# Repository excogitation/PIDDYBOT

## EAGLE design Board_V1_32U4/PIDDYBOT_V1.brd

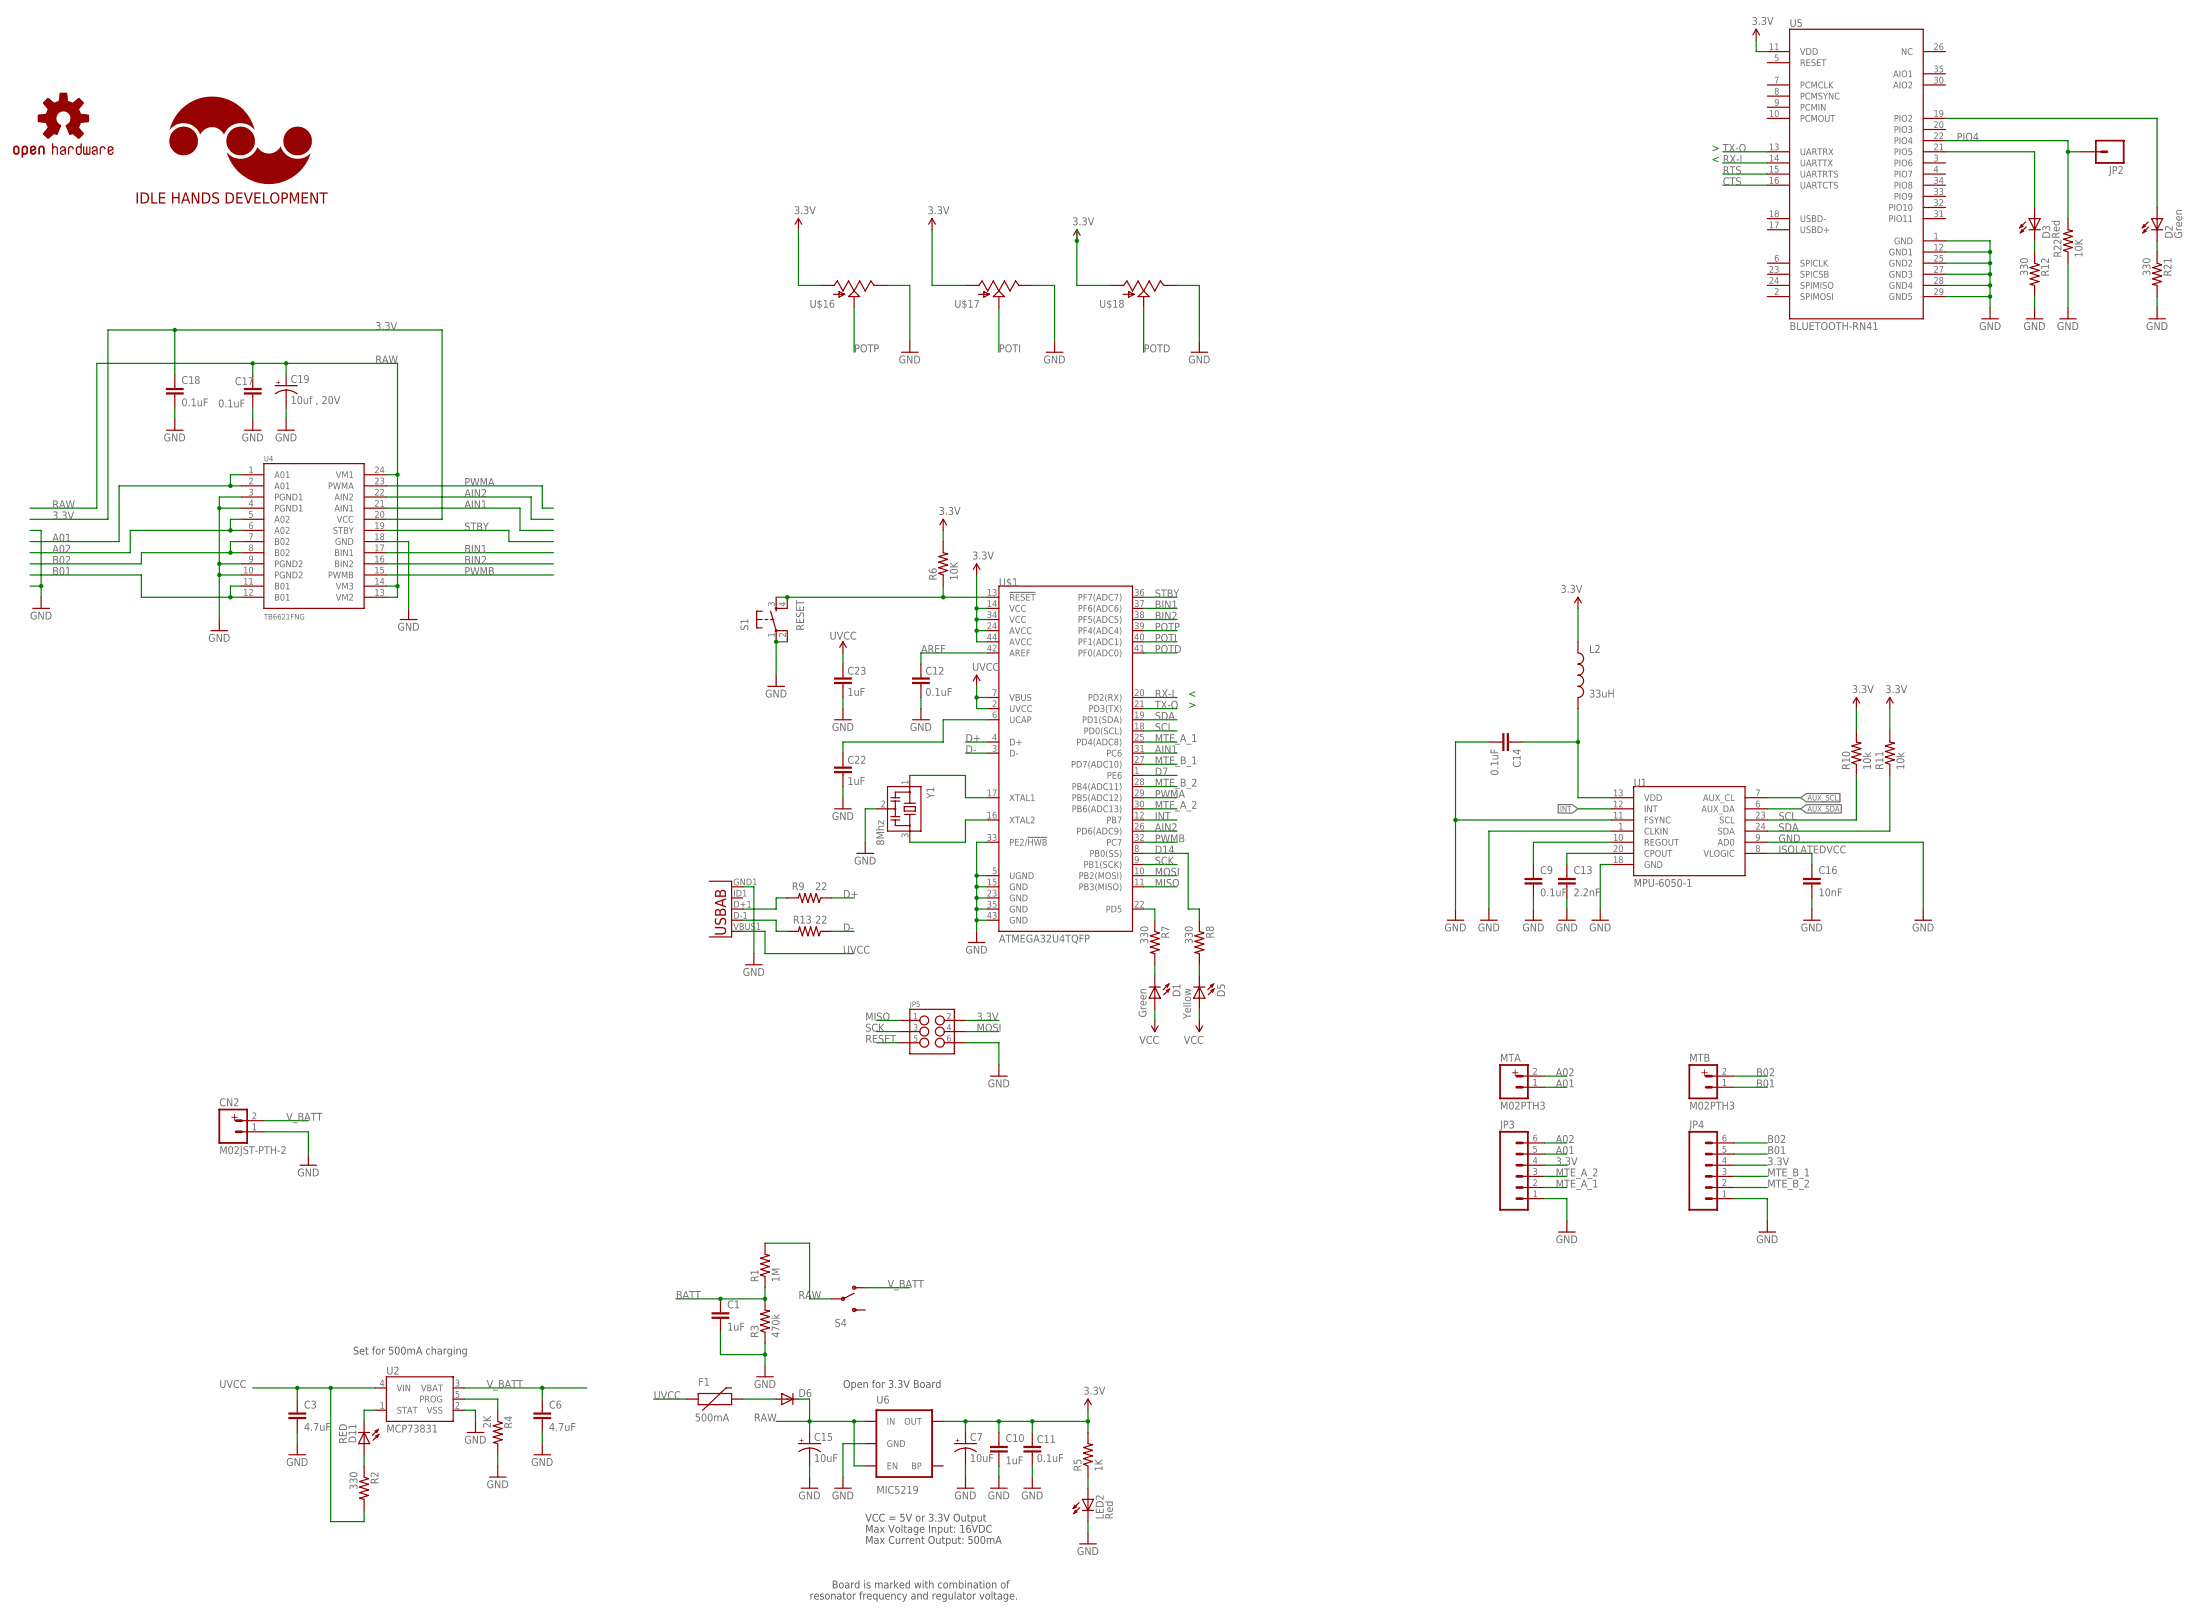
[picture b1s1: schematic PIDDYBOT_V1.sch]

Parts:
C1, C10, C22, C23: 1uF; 0603-CAP
C3, C6: 4.7uF; 0603-CAP
C7, C15: 10uF; EIA3216
C9, C11, C12, C14, C17, C18: 0.1uF; 0603-CAP
C13: 2.2nF; 0603-CAP
C16: 10nF; 0603-CAP
C19: 10uf , 20V; EIA3528
CN2: M02JST-PTH-2; JST-2-PTH
D1, D2: Green; LED-0603
D3: Red; LED-0603
D5: Yellow; LED-0603
D6: DIODESOD; SOD-323
D11: RED; LED-0603
F1: 500mA; PTC-1206
JP2: M01SMDNS; 1X01NS
JP3, JP4: M06SMD-1MM; 1X06-1MM
JP5: M03X2NO_SILK; 2X3-NS
L2: 33uH; C0402
LED2: Red; LED-0603
LOGO1: IDLEHANDS_LOGOL; IHD-LOGO-L
LOGO2: OSHW-LOGOM; OSHW-LOGO-M
MTA: M02PTH3; 1X02_LONGPADS
MTB: M02PTH3; 1X02_LONGPADS
R1: 1M; 0603-RES
R2, R7, R8, R12, R21: 330; 0603-RES
R3: 470k; 0603-RES
R4: 2K; 0603-RES
R5: 1K; 0603-RES
R6, R22: 10K; 0603-RES
R9, R13: 22; 0603-RES
R10, R11: 10k; 0603-RES
S1: RESET; TACTILE_SWITCH_SMD
S4: SWITCH-SPDTPTH; SWITCH-SPDT
U1: MPU-6050-1; QFN-24-4MM2
U2: MCP73831; SOT23-5
U4: TB6621FNG; SSOP24
U5: BLUETOOTH-RN41; RN41
U6: MIC5219; SOT23-5
U$1: ATMEGA32U4TQFP; SPARKFUN-DIGITALIC_TQFP44
U$16, U$17, U$18: POT; ALPS_POT
X2: USB-ABIN&OUT; USB-AB-MICRO-SMD-V03-IN&OUT
Y1: 8Mhz; CSTCR6M

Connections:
3.3V: C7.A (+), C10.1, C11.2, C18.1, D1.A, D5.A, JP3.4, JP4.4, JP5.2, L2.1, R5.2, R6.2, R10.2, R11.2, U4.20 (VCC), U5.11 (VDD), U6.5 (OUT), U$1.14 (VCC), U$1.24 (AVCC), U$1.34 (VCC), U$1.44 (AVCC), U$16.P$3 (A), U$17.P$3 (A), U$18.P$3 (A)
A01: JP3.5, MTA.1, U4.1 (A01), U4.2 (A01)
A02: JP3.6, MTA.2, U4.5 (A02), U4.6 (A02)
AIN1: U4.21 (AIN1), U$1.31 (PC6)
AIN2: U4.22 (AIN2), U$1.26 (PD6(ADC9))
AREF: C12.2, U$1.42 (AREF)
AUX_SCL: U1.7 (AUX_CL)
AUX_SDA: U1.6 (AUX_DA)
B01: JP4.5, MTB.1, U4.11 (B01), U4.12 (B01)
B02: JP4.6, MTB.2, U4.7 (B02), U4.8 (B02)
BATT: C1.1, R1.1, R3.2
BIN1: U4.17 (BIN1), U$1.37 (PF6(ADC6))
BIN2: U4.16 (BIN2), U$1.38 (PF5(ADC5))
CTS: U5.16 (UARTCTS)
D1: D3.C, R12.1
D2: D2.C, R21.1
D7: U$1.1 (PE6)
D14: R8.1, U$1.8 (PB0(SS))
D+: R9.1, U$1.4 (D+)
D-: R13.1, U$1.3 (D-)
GND: C1.2, C3.2, C6.2, C7.C (-), C9.2, C10.2, C11.1, C12.1, C13.2, C14.2, C15.C (-), C16.2, C17.2, C18.2, C19.C (-), C22.1, C23.1, CN2.1, JP3.1, JP4.1, JP5.6, LED2.C, R3.1, R4.2, R12.2, R21.2, R22.1, S1.1, S1.2, U1.1 (CLKIN), U1.9 (AD0), U1.11 (FSYNC), U1.18 (GND), U2.2 (VSS), U4.3 (PGND1), U4.4 (PGND1), U4.9 (PGND2), U4.10 (PGND2), U4.18 (GND), U5.1 (GND), U5.12 (GND1), U5.25 (GND2), U5.27 (GND3), U5.28 (GND4), U5.29 (GND5), U6.2 (GND), U$1.5 (UGND), U$1.15 (GND), U$1.23 (GND), U$1.33 (PE2/!HWB), U$1.35 (GND), U$1.43 (GND), U$16.P$1 (E), U$17.P$1 (E), U$18.P$1 (E), X2.GND1 (GND), Y1.2
INT: U1.12 (INT), U$1.12 (PB7)
ISOLATEDVCC: C14.1, C16.1, L2.2, U1.8 (VLOGIC), U1.13 (VDD)
MISO: JP5.1, U$1.11 (PB3(MISO))
MOSI: JP5.4, U$1.10 (PB2(MOSI))
MTE_A_1: JP3.2, U$1.25 (PD4(ADC8))
MTE_A_2: JP3.3, U$1.30 (PB6(ADC13))
MTE_B_1: JP4.3, U$1.27 (PD7(ADC10))
MTE_B_2: JP4.2, U$1.28 (PB4(ADC11))
unnamed: U$1.17 (XTAL1), Y1.1
unnamed: U$1.16 (XTAL2), Y1.3
unnamed: D6.2 (A), F1.2
unnamed: C13.1, U1.20 (CPOUT)
unnamed: C9.1, U1.10 (REGOUT)
unnamed: D3.A, U5.21 (PIO5)
unnamed: D2.A, U5.19 (PIO2)
unnamed: D11.A, R2.1
unnamed: C22.2, U$1.6 (UCAP)
unnamed: R13.2, X2.D-1 (D-)
unnamed: R9.2, X2.D+1 (D+)
unnamed: D5.C, R8.2
unnamed: D1.C, R7.2
unnamed: LED2.A, R5.1
PIO4: JP2.1, R22.2, U5.22 (PIO4)
POTD: U$1.41 (PF0(ADC0)), U$18.P$2 (S)
POTI: U$1.40 (PF1(ADC1)), U$17.P$2 (S)
POTP: U$1.39 (PF4(ADC4)), U$16.P$2 (S)
PROG: R4.1, U2.5 (PROG)
PWMA: U4.23 (PWMA), U$1.29 (PB5(ADC12))
PWMB: U4.15 (PWMB), U$1.32 (PC7)
RAW: C15.A (+), C17.1, C19.A (+), D6.1 (C), R1.2, S4.2, U4.13 (VM2), U4.14 (VM3), U4.24 (VM1), U6.1 (IN), U6.3 (EN)
RESET: JP5.5, R6.1, S1.3, S1.4, U$1.13 (!RESET)
RTS: U5.15 (UARTRTS)
RX-I: U5.14 (UARTTX), U$1.20 (PD2(RX))
SCK: JP5.3, U$1.9 (PB1(SCK))
SCL: R10.1, U1.23 (SCL), U$1.18 (PD0(SCL))
SDA: R11.1, U1.24 (SDA), U$1.19 (PD1(SDA))
STAT: D11.C, U2.1 (STAT)
STBY: U4.19 (STBY), U$1.36 (PF7(ADC7))
TX-O: U5.13 (UARTRX), U$1.21 (PD3(TX))
TXLED: R7.1, U$1.22 (PD5)
UVCC: C3.1, C23.2, F1.1, R2.2, U2.4 (VIN), U$1.2 (UVCC), U$1.7 (VBUS), X2.VBUS1 (VBUS)
V_BATT: C6.1, CN2.2, S4.1 (O), U2.3 (VBAT)

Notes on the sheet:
Set for 500mA charging
Max Voltage Input: 16VDC
Max Current Output: 500mA
Board is marked with combination of
resonator frequency and regulator voltage.
VCC = 5V or 3.3V Output
Open for 3.3V Board

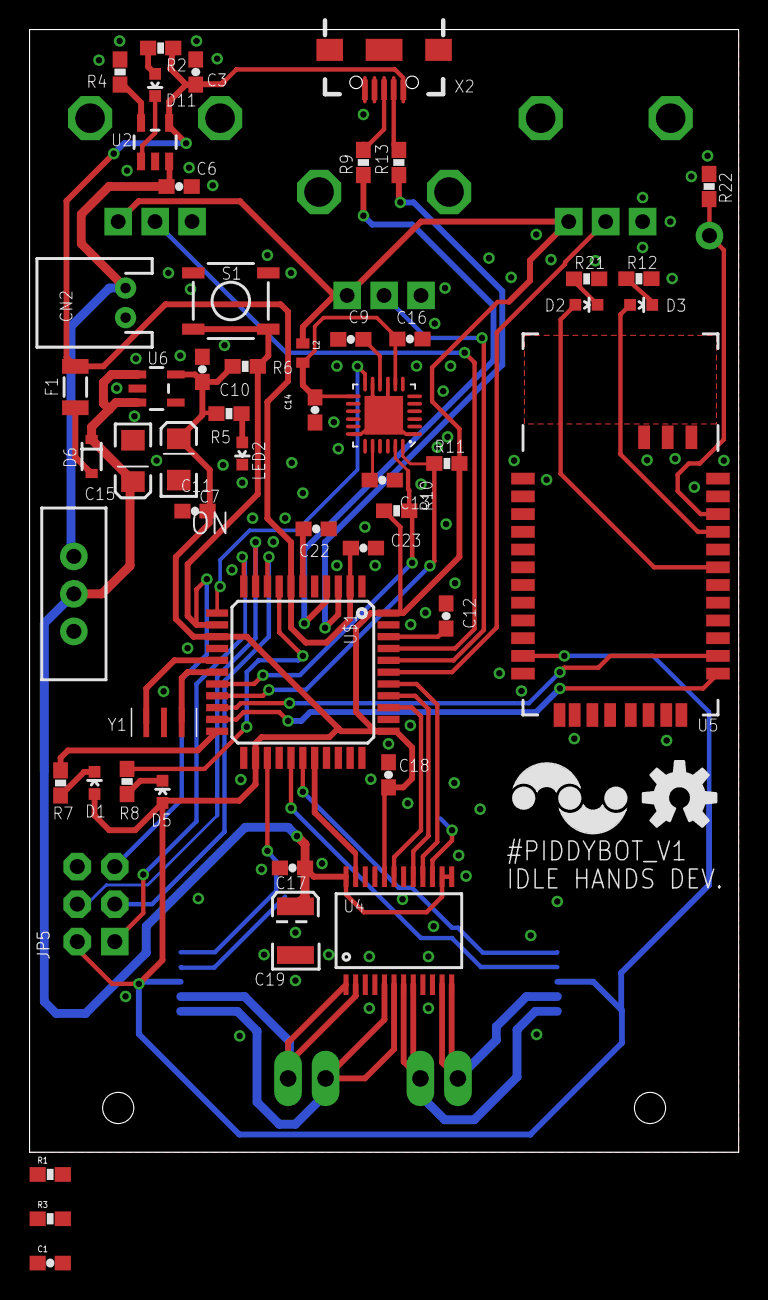
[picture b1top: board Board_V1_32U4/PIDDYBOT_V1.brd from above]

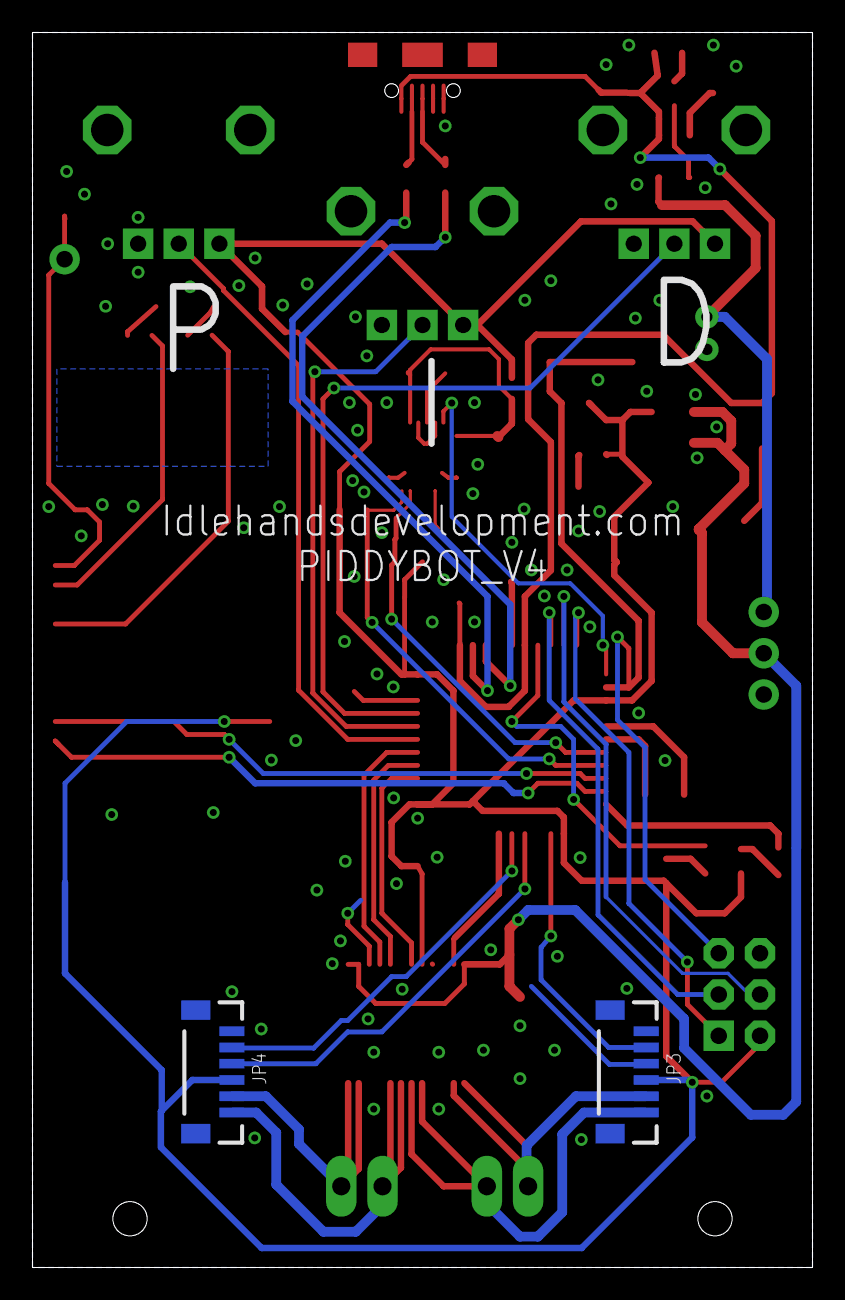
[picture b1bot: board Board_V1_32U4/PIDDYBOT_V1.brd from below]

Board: 2 copper layers, 48.0 x 76.0 mm, 63 parts (5 on the bottom side), 58 nets.

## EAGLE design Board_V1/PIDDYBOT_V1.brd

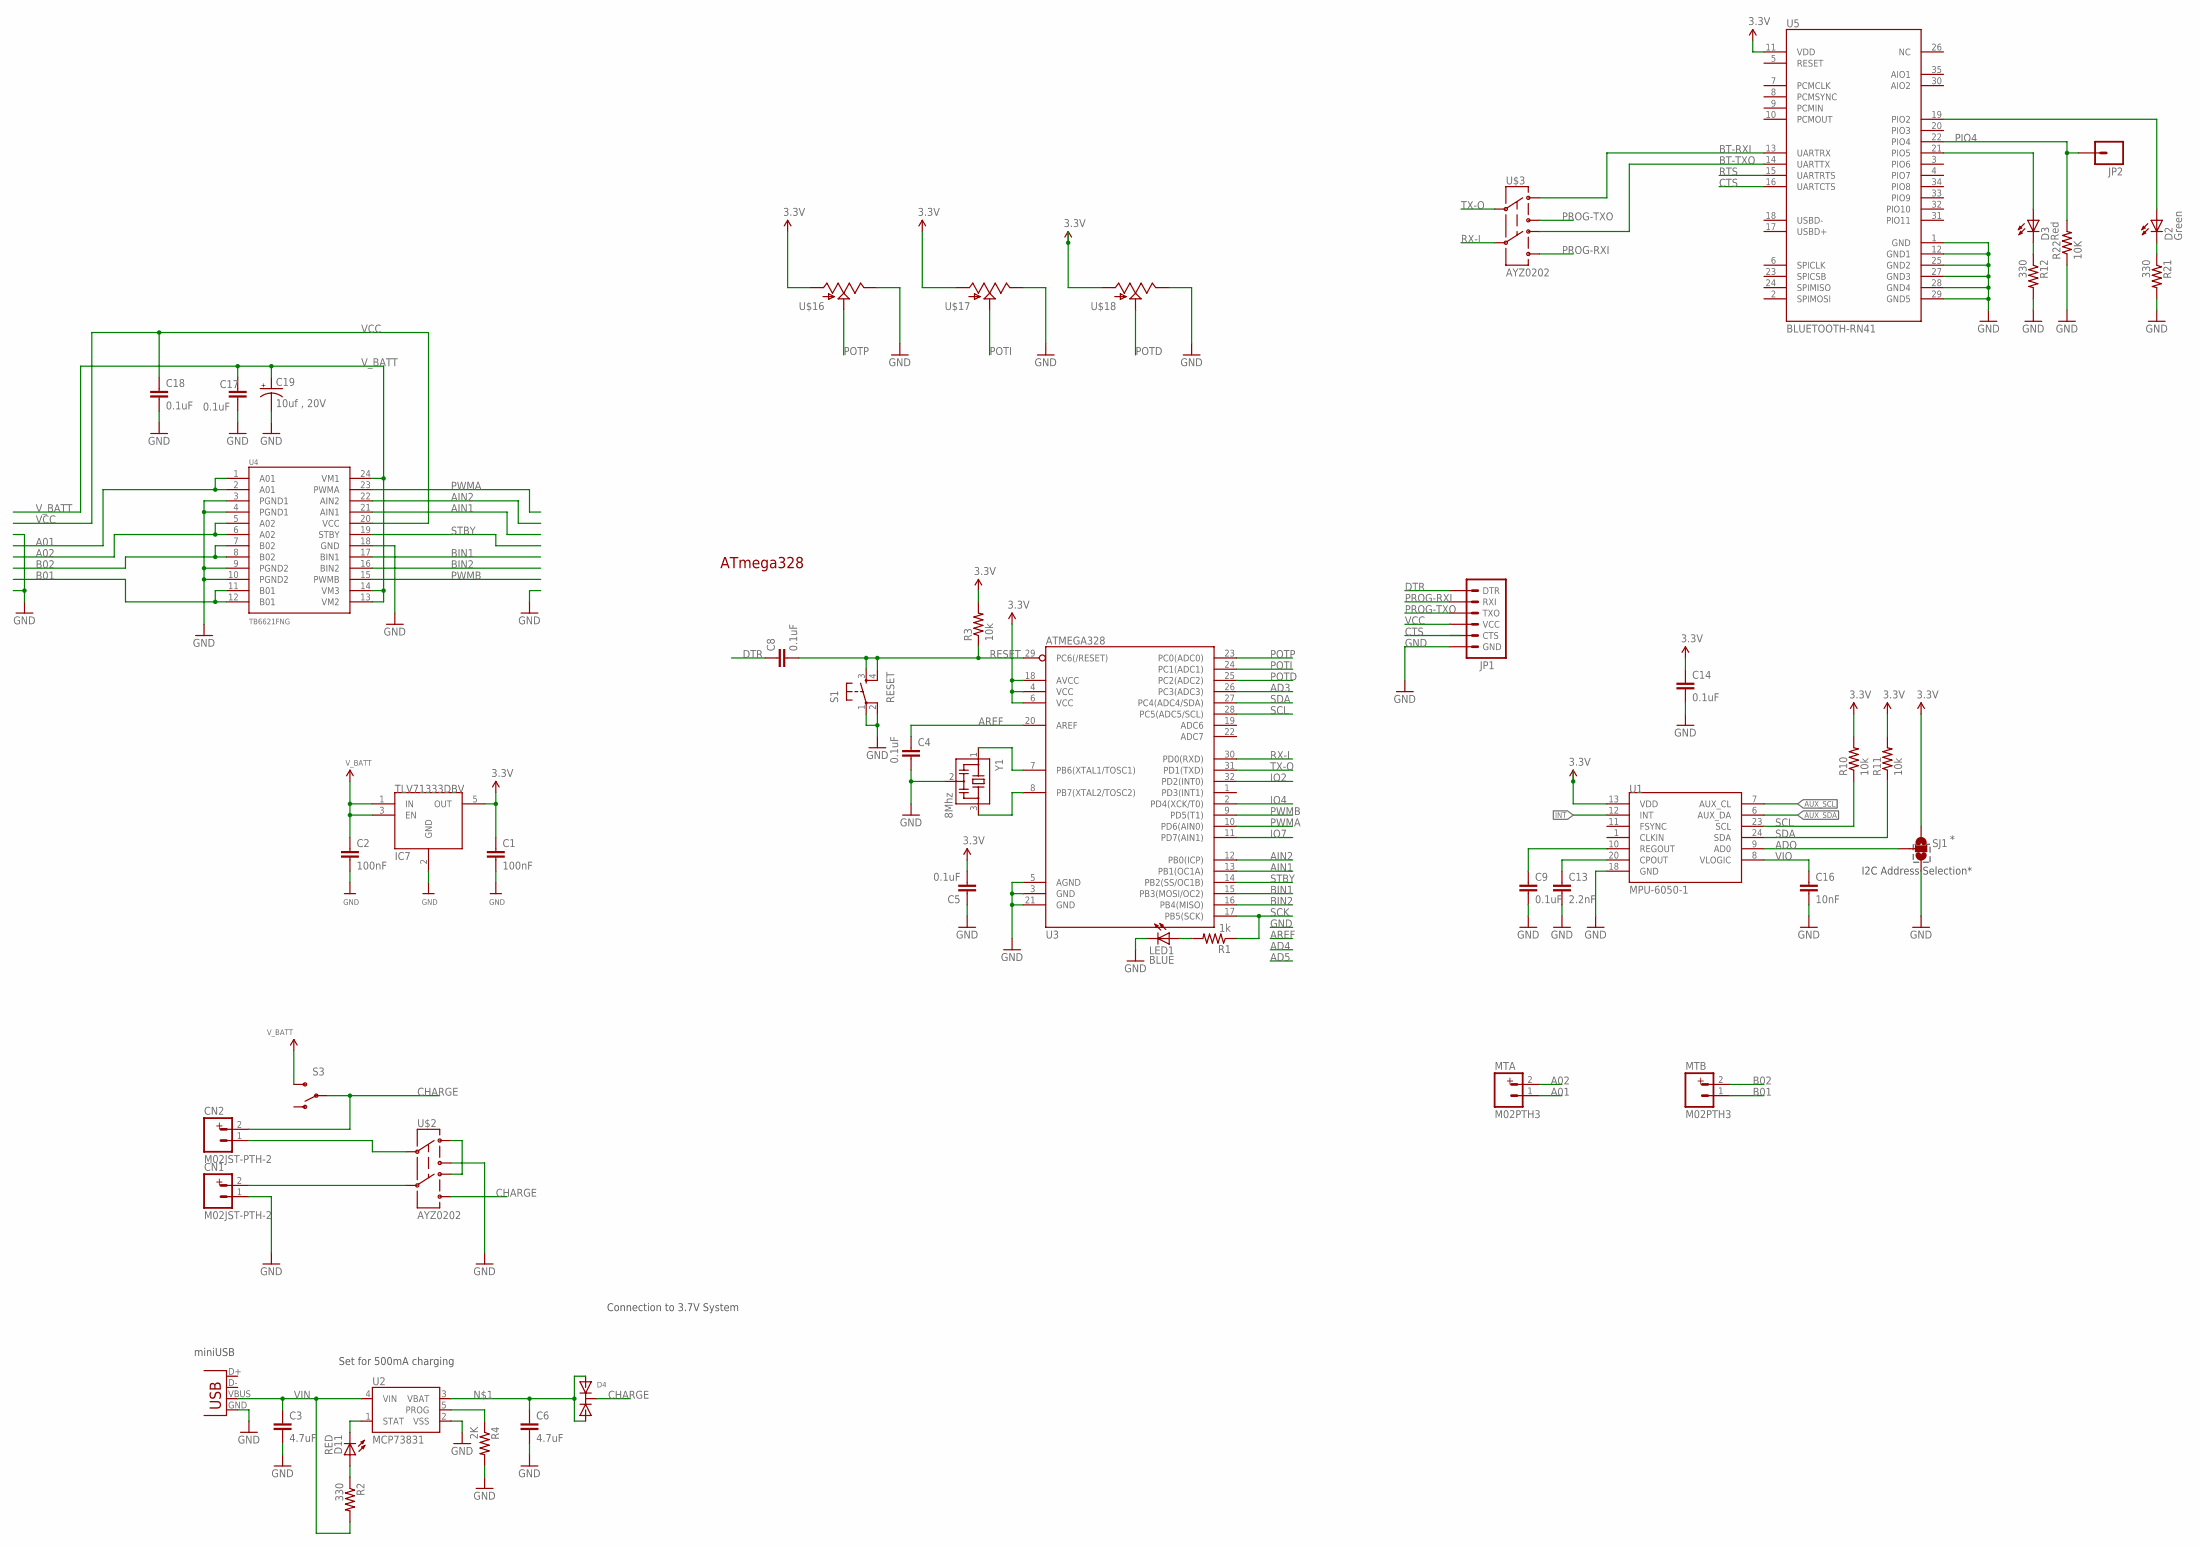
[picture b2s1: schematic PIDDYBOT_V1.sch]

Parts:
C1, C2: 100nF; C0603K
C3, C6: 4.7uF; 0402-CAP
C4, C5, C8, C17, C18: 0.1uF; 0402-CAP
C9, C14: 0.1uF; 0603-CAP
C13: 2.2nF; 0603-CAP
C16: 10nF; 0603-CAP
C19: 10uf , 20V; EIA3528
CN1, CN2: M02JST-PTH-2; JST-2-PTH
D2: Green; LED-0603
D3: Red; LED-0603
D4: BAT54C; SOT23-R
D11: RED; LED-0603
IC7: TLV71333DBV; SOT-23-5
JP1: ARDUINO_SERIAL_PROGRAMSMD; 1X06-SMD
JP2: M01SMDNS; 1X01NS
LED1: BLUE; LED-0603
MTA: M02PTH3; 1X02_LONGPADS
MTB: M02PTH3; 1X02_LONGPADS
R1: 1k; 0402-RES
R2, R12, R21: 330; 0402-RES
R3: 10k; 0402-RES
R4: 2K; 0402-RES
R10, R11: 10k; 0603-RES
R22: 10K; 0402-RES
S1: RESET; TACTILE_SWITCH_SMD
S3: SWITCH-SPDTPTH; SWITCH-SPDT
SJ1: SOLDERJUMPER_2WAYPASTE2&3; SJ_3_PASTE2&3
U1: MPU-6050-1; QFN-24-4MM2
U2: MCP73831; SOT23-5
U3: ATMEGA328; TQFP32-08
U4: TB6621FNG; SSOP24
U5: BLUETOOTH-RN41; RN41
U$2, U$3: AYZ0202
U$16, U$17, U$18: POT; ALPS_POT
X1: Micro USB; USB-MINIB
Y1: 8Mhz; CSTCR6M

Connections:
A01: MTA.1, U4.1 (A01), U4.2 (A01)
A02: MTA.2, U4.5 (A02), U4.6 (A02)
AD3: U3.26 (PC3(ADC3))
ADO: SJ1.2, U1.9 (AD0)
AIN1: U3.13 (PB1(OC1A)), U4.21 (AIN1)
AIN2: U3.12 (PB0(ICP)), U4.22 (AIN2)
AREF: C4.1, U3.20 (AREF)
AUX_SCL: U1.7 (AUX_CL)
AUX_SDA: U1.6 (AUX_DA)
B01: MTB.1, U4.11 (B01), U4.12 (B01)
B02: MTB.2, U4.7 (B02), U4.8 (B02)
BIN1: U3.15 (PB3(MOSI/OC2)), U4.17 (BIN1)
BIN2: U3.16 (PB4(MISO)), U4.16 (BIN2)
BT-RXI: U5.13 (UARTRX), U$3.3 (1)
BT-TXO: U5.14 (UARTTX), U$3.6 (4)
CHARGE: CN2.2, D4.3 (C), S3.2, U$2.4 (6)
CTS: U5.16 (UARTCTS)
D1: D3.C, R12.1
D2: D2.C, R21.1
DTR: C8.1, JP1.1 (DTR)
GND: C1.2, C2.2, C3.2, C4.2, C5.1, C6.2, C9.2, C13.2, C14.2, C16.2, C17.2, C18.2, C19.C (-), CN1.1, IC7.2 (GND), JP1.6 (GND), LED1.C, R4.2, R12.2, R21.2, R22.1, S1.1, S1.2, SJ1.3, U1.18 (GND), U2.2 (VSS), U3.3 (GND), U3.5 (AGND), U3.21 (GND), U4.3 (PGND1), U4.4 (PGND1), U4.9 (PGND2), U4.10 (PGND2), U4.18 (GND), U5.1 (GND), U5.12 (GND1), U5.25 (GND2), U5.27 (GND3), U5.28 (GND4), U5.29 (GND5), U$2.1 (3), U$16.P$1 (E), U$17.P$1 (E), U$18.P$1 (E), X1.GND, Y1.2
INT: U1.12 (INT)
IO2: U3.32 (PD2(INT0))
IO4: U3.2 (PD4(XCK/T0))
IO7: U3.11 (PD7(AIN1))
unnamed: C6.1, D4.1 (A1), D4.2 (A2), U2.3 (VBAT)
unnamed: CN2.1, U$2.2
unnamed: LED1.A, R1.2
unnamed: U3.7 (PB6(XTAL1/TOSC1)), Y1.1
unnamed: U3.8 (PB7(XTAL2/TOSC2)), Y1.3
unnamed: C13.1, U1.20 (CPOUT)
unnamed: C9.1, U1.10 (REGOUT)
unnamed: CN1.2, U$2.5
unnamed: D3.A, U5.21 (PIO5)
unnamed: U$2.3 (1), U$2.6 (4)
unnamed: D2.A, U5.19 (PIO2)
unnamed: D11.A, R2.1
PIO4: JP2.1, R22.2, U5.22 (PIO4)
POTD: U3.25 (PC2(ADC2)), U$18.P$2 (S)
POTI: U3.24 (PC1(ADC1)), U$17.P$2 (S)
POTP: U3.23 (PC0(ADC0)), U$16.P$2 (S)
PROG: R4.1, U2.5 (PROG)
PROG-RXI: JP1.2 (RXI), U$3.4 (6)
PROG-TXO: JP1.3 (TXO), U$3.1 (3)
PWMA: U3.10 (PD6(AIN0)), U4.23 (PWMA)
PWMB: U3.9 (PD5(T1)), U4.15 (PWMB)
RESET: C8.2, R3.1, S1.3, S1.4, U3.29 (PC6(/RESET))
RTS: U5.15 (UARTRTS)
RX-I: U3.30 (PD0(RXD)), U$3.5
SCK: R1.1, U3.17 (PB5(SCK))
SCL: R10.1, U1.23 (SCL), U3.28 (PC5(ADC5/SCL))
SDA: R11.1, U1.24 (SDA), U3.27 (PC4(ADC4/SDA))
STAT: D11.C, U2.1 (STAT)
STBY: U3.14 (PB2(SS/OC1B)), U4.19 (STBY)
TX-O: U3.31 (PD1(TXD)), U$3.2
VCC: C1.1, C5.2, C14.1, C18.1, IC7.5 (OUT), JP1.4 (VCC), R3.2, R10.2, R11.2, SJ1.1, U1.13 (VDD), U3.4 (VCC), U3.6 (VCC), U3.18 (AVCC), U4.20 (VCC), U5.11 (VDD), U$16.P$3 (A), U$17.P$3 (A), U$18.P$3 (A)
VIN: C3.1, R2.2, U2.4 (VIN), X1.VBUS
VIO: C16.1, U1.8 (VLOGIC)
V_BATT: C2.1, C17.1, C19.A (+), IC7.1 (IN), IC7.3 (EN), S3.3 (S), U4.13 (VM2), U4.14 (VM3), U4.24 (VM1)

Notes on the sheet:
ATmega328
I2C Address Selection*
Set for 500mA charging
Connection to 3.7V System
miniUSB

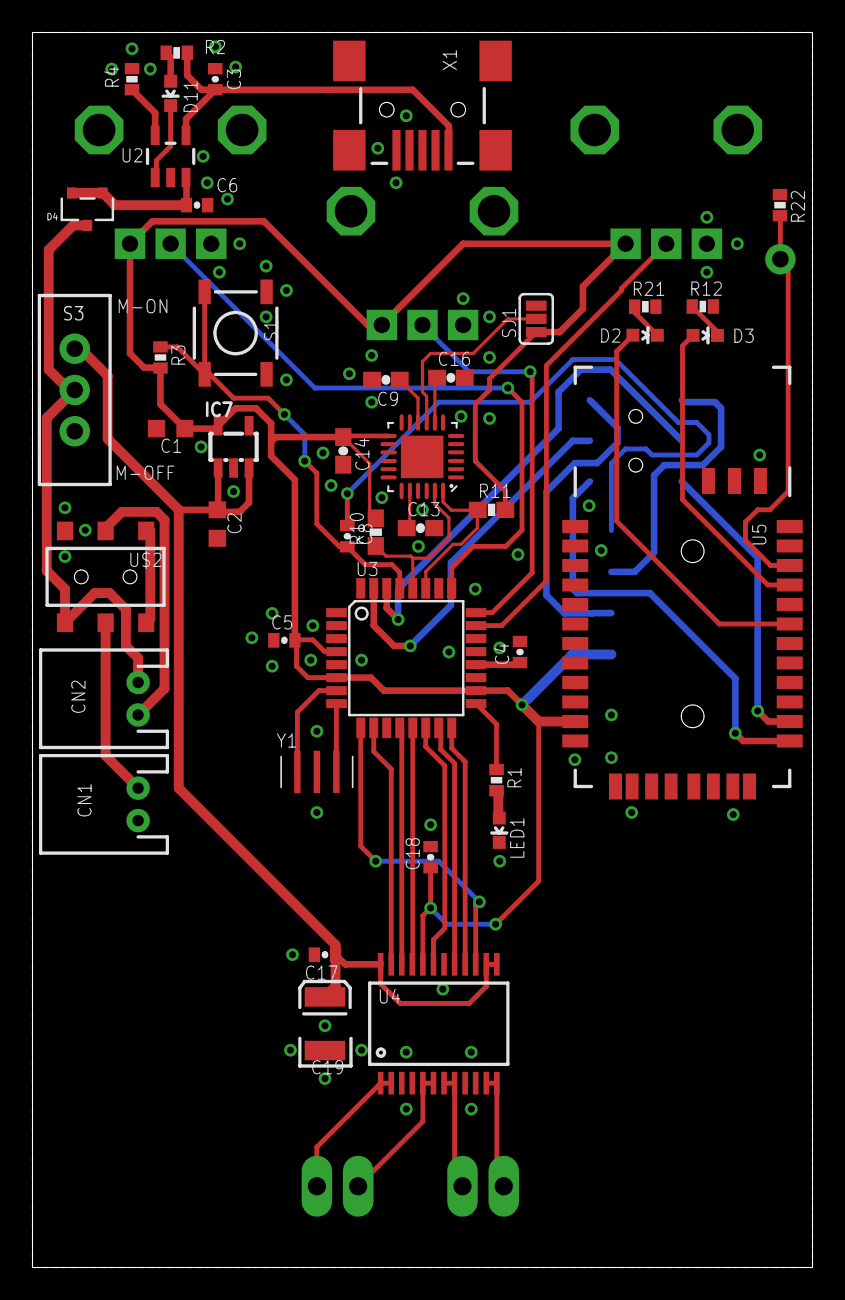
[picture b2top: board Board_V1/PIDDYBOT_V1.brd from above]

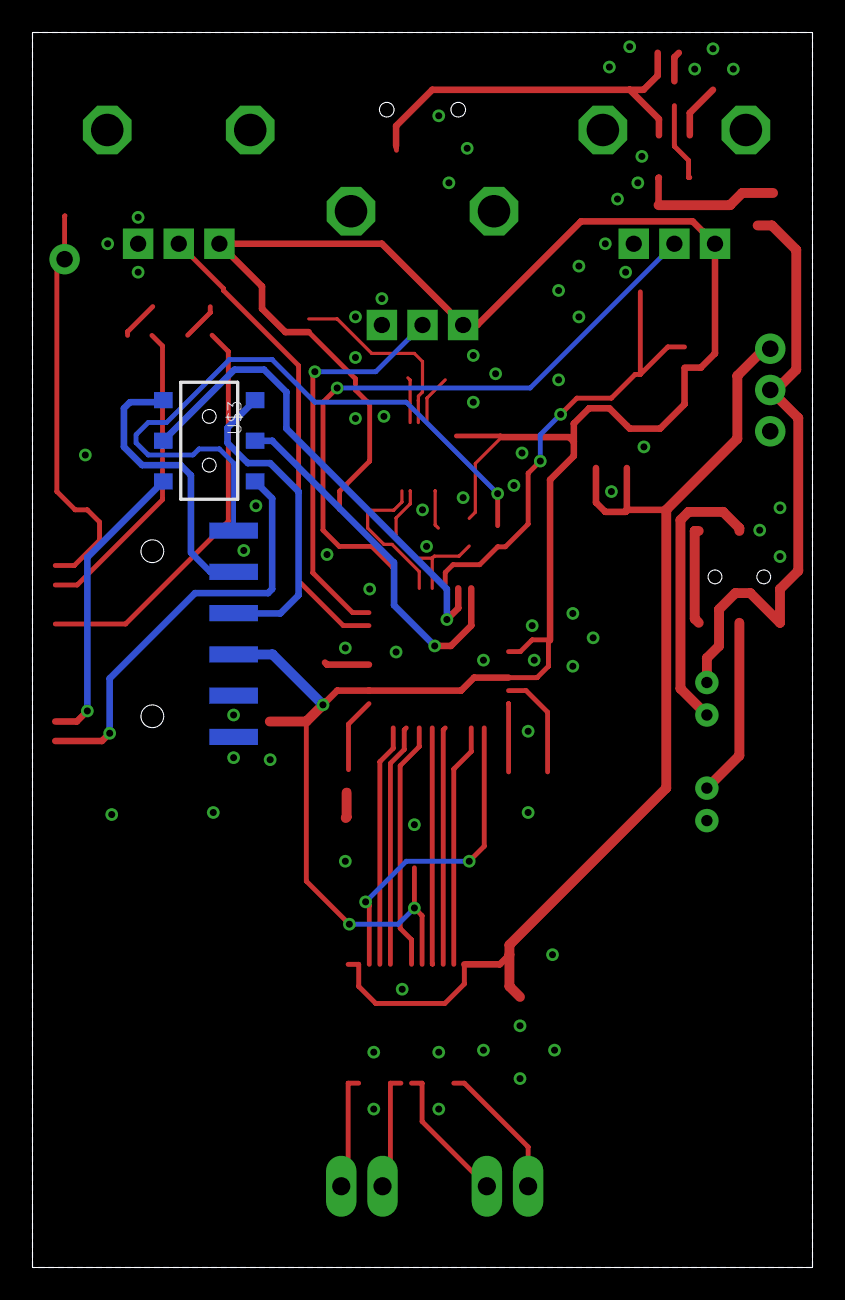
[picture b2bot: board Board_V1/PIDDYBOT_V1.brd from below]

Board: 2 copper layers, 48.0 x 76.0 mm, 50 parts (5 on the bottom side), 50 nets.

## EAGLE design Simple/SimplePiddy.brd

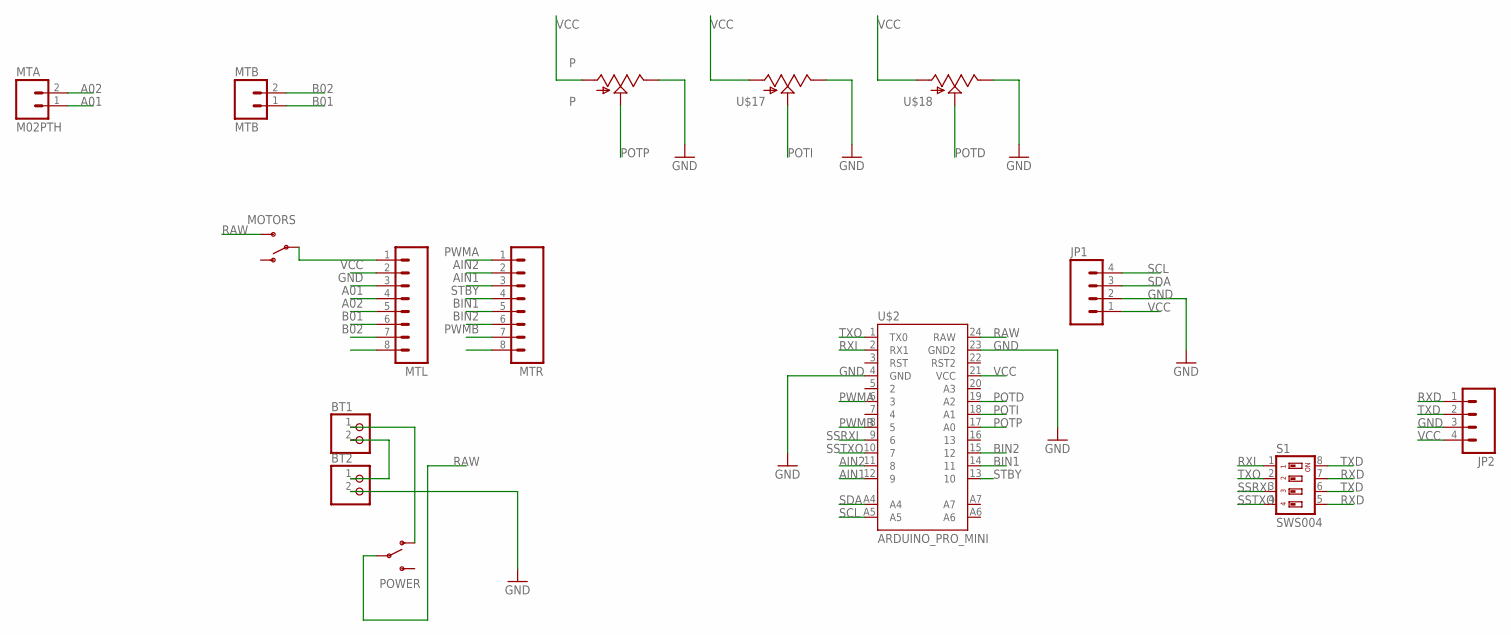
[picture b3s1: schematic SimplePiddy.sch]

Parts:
BT1, BT2: JST_2PIN; JSTPH2STRAIGHT
JP1, JP2: M04PTH; 1X04
MOTORS: SWITCH-SPDTPTH; SWITCH-SPDT
MTA: M02PTH; 1X02
MTB: MTB; 1X02
MTL: M08LONGPADS; 1X08_LONGPADS
MTR: M08LONGPADS; 1X08_LONGPADS
P: P; ALPS_POT
POWER: SWITCH-SPDTPTH; SWITCH-SPDT
S1: SWS004; SMS-004
U$2: ARDUINO_PRO_MINI
U$17, U$18: POT; ALPS_POT

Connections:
A01: MTA.1, MTL.4
A02: MTA.2, MTL.5
AIN1: MTR.3, U$2.12 (9)
AIN2: MTR.2, U$2.11 (8)
B01: MTB.1, MTL.6
B02: MTB.2, MTL.7
BIN1: MTR.5, U$2.14 (11)
BIN2: MTR.6, U$2.15 (12)
GND: BT2.2, JP1.2, JP2.3, MTL.3, MTL.8, MTR.8, P.P$1 (E), U$2.4 (GND), U$2.23 (GND2), U$17.P$1 (E), U$18.P$1 (E)
unnamed: MOTORS.2, MTL.1
unnamed: BT1.2, BT2.1
unnamed: BT1.1, POWER.1 (O)
POTD: U$2.19 (A2), U$18.P$2 (S)
POTI: U$2.18 (A1), U$17.P$2 (S)
POTP: P.P$2 (S), U$2.17 (A0)
PWMA: MTR.1, U$2.6 (3)
PWMB: MTR.7, U$2.8 (5)
RAW: MOTORS.3 (S), POWER.2, U$2.24 (RAW)
RXD: JP2.1, S1.5, S1.7
RXI: S1.1, U$2.2 (RX1)
SCL: JP1.4, U$2.A5
SDA: JP1.3, U$2.A4
SSRXI: S1.3, U$2.9 (6)
SSTXO: S1.4, U$2.10 (7)
STBY: MTR.4, U$2.13 (10)
TXD: JP2.2, S1.6, S1.8
TXO: S1.2, U$2.1 (TX0)
VCC: JP1.1, JP2.4, MTL.2, P.P$3 (A), U$2.21 (VCC), U$17.P$3 (A), U$18.P$3 (A)

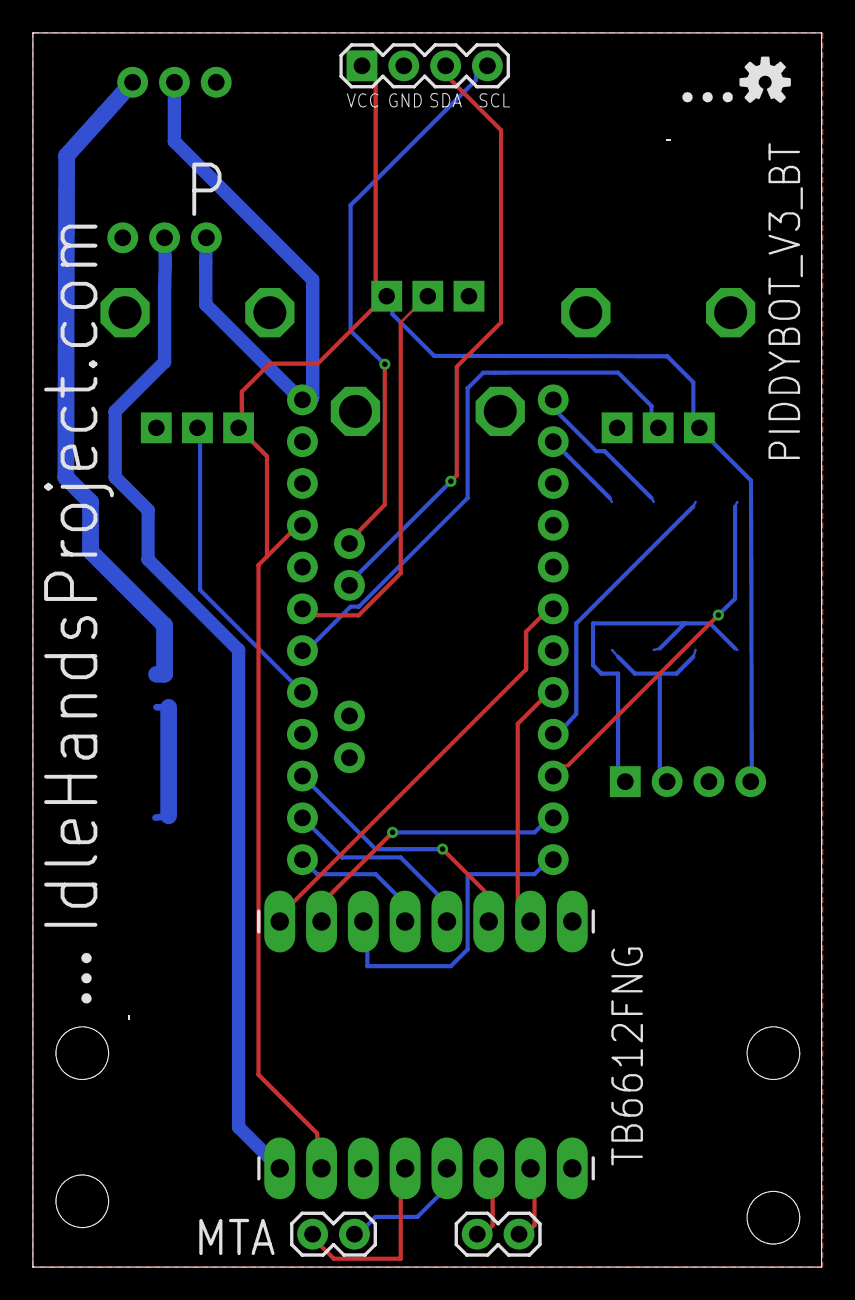
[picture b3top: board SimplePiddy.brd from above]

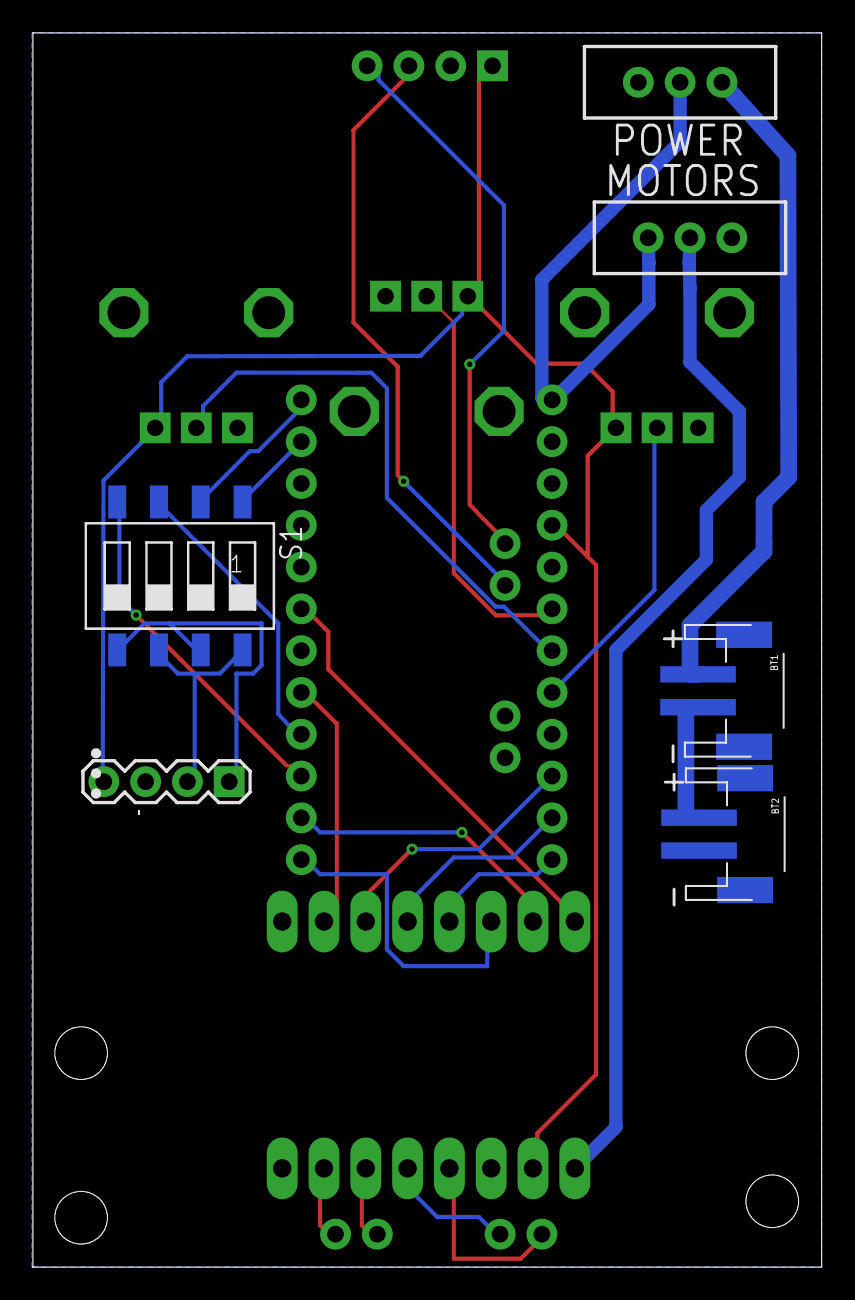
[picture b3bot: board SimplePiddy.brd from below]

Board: 2 copper layers, 47.9 x 75.0 mm, 19 parts (8 on the bottom side), 28 nets.

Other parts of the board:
U$1: OSHW-LOGO-S
U$3, U$4, U$5: ELIPSISLOGO-3MM

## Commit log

2014-02-17 Two PIDDYBOT Boards created.
    Added to repo.
2014-05-30 Lots of Updates
    Created second Simple Piddy.
    Updates to Complex Piddy
2014-07-25 added gitignore for folders
2014-08-06 Latest PIDDYBOT pcb finished ready to order
2014-09-03 Modified brd file
2014-09-03 Changed power line for v_batt to v_motor
2014-10-28 latest PIDDYBOT 32u4 update

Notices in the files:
parts and their libraries:
SparkFun-Connectors: Licensing: CC v3.0 Share-Alike You are welcome to use this library for commercial purposes.
